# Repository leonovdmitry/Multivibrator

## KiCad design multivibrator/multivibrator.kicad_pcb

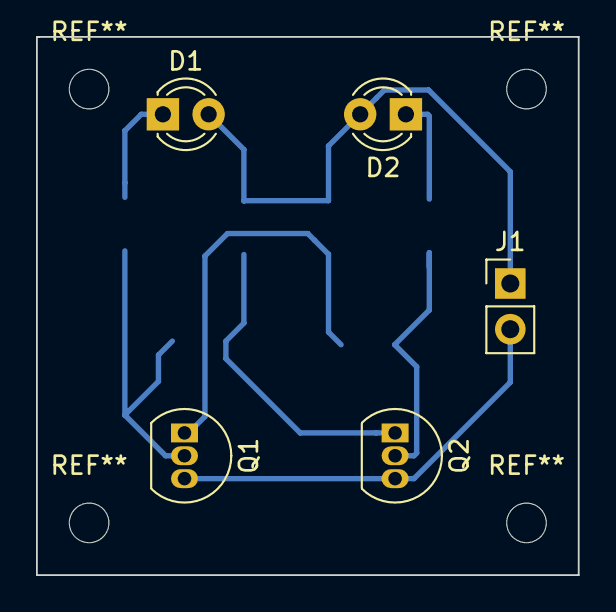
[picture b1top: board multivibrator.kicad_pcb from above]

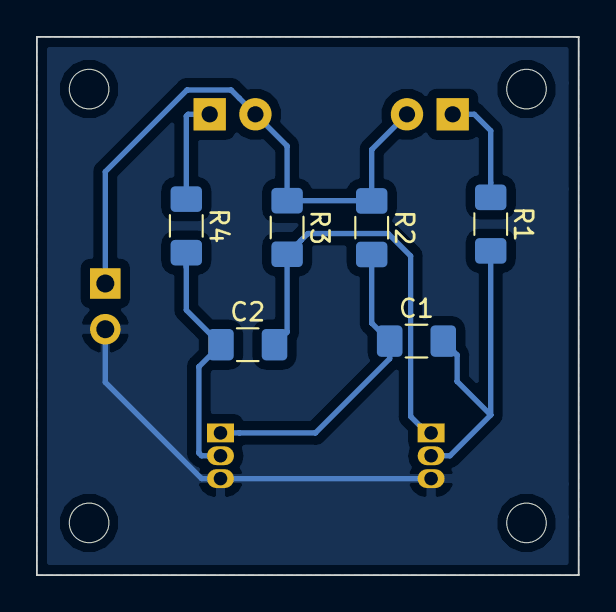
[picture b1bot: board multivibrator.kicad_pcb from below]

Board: 2 copper layers, 30.1 x 29.9 mm, 11 parts (6 on the bottom side), 8 nets.

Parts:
C1, C2: C; C_1206_3216Metric_Pad1.42x1.75mm_HandSolder
D1, D2: LED; LED_D3.0mm
J1: Conn_01x02_Female; PinHeader_1x02_P2.54mm_Vertical
Q1, Q2: Q_NPN_BCE; TO-92_Inline
R1, R2, R3, R4: R; R_1206_3216Metric_Pad1.42x1.75mm_HandSolder

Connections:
unnamed: C1.1, Q2.1, R2.2
unnamed: C1.2, Q1.2, R1.2
unnamed: C2.1, Q2.2, R4.2
unnamed: C2.2, Q1.1, R3.2
unnamed: D1.1, R1.1
unnamed: D1.2, D2.2, J1.1, R2.1, R3.1
unnamed: D2.1, R4.1
unnamed: J1.2, Q1.3, Q2.3

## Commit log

2018-09-23 add schema
2018-09-27 improvement
2018-09-30 review fixes, ready for print
